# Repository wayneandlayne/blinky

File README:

This is the code for the Blinky POV and Blinky GRID kits from Wayne and Layne.
More information: http://www.wayneandlayne.com/projects/blinky/

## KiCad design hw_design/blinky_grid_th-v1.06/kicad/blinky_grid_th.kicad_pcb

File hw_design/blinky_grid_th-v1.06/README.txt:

Wayne and Layne present:
Blinky Grid TH - Hardware v1.06

These are the design files, for use with Kicad, an open source electronic design suite available for Windows, Linux, and OS X.

More details are available at http://www.wayneandlayne.com/projects/blinky/

Design files: (Located in kicad/ subdirectory)
-------------
blinky_grid_th.brd                  PCB layout
blinky_grid_th.cmp                  Symbol to footprint mapping
blinky_grid_th.net                  Netlist
blinky_grid_th.pro                  Kicad project file
blinky_grid_th.sch                  Schematic
wayne_and_layne_kicad_modules.mod   W&L footprint library
wayne_and_layne_kicad_symbols.lib   W&L symbol library

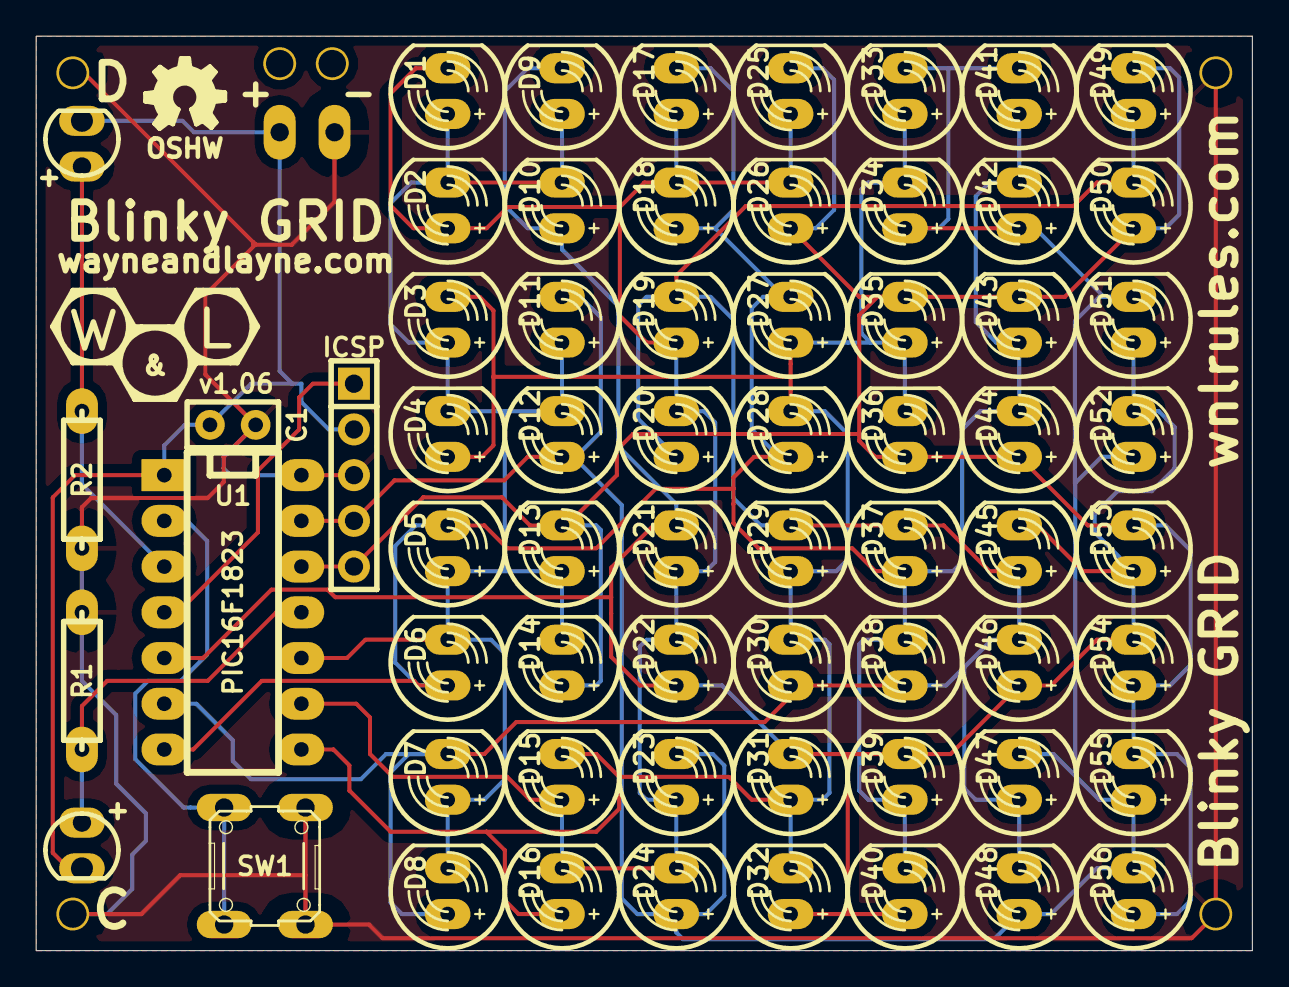
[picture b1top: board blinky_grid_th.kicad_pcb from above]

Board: 2 copper layers, 67.6 x 50.8 mm, 69 parts (0 on the bottom side), 14 nets.

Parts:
BT1: BATTERY; WNL_BATHOLES
C1: C; WNL_C1
D1, D2, D3, D4, D5, D6, D7, D8, D9, D10, D11, D12, D13, D14, D15, D16, D17, D18, D19, D20, D21, D22, D23, D24, D25, D26, D27, D28, D29, D30, D31, D32, D33, D34, D35, D36, D37, D38, D39, D40, D41, D42, D43, D44, D45, D46, D47, D48, D49, D50, D51, D52, D53, D54, D55, D56: LED; LED_5MM_PRETTY_BIGPADS
D57: SCLK; WNL_LIGHTSENSOR_3MM
D58: SDAT; WNL_LIGHTSENSOR_3MM
P1: ICSP; WNL_SIL_5
P2, P3, P4, P5: MOUNT; 1pin60mil
R1, R2: 10K; WNL_R3
SW1: SW_PUSH; WNL_OMRON_6MM_PRETTY
U1: PIC16F1823; WNL_DIP_14_300

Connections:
/BUTTON: SW1.1, U1.2
/LED0: D1.1, D2.2, D3.1, D4.2, D5.1, D6.2, D7.1, D8.2, D9.1, D10.2, D11.1, D12.2, D13.1, D14.2, U1.10
/LED1: D1.2, D2.1, D15.1, D16.2, D17.1, D18.2, D19.1, D20.2, D21.1, D22.2, D23.1, D24.2, D25.1, D26.2, U1.9
/LED2: D3.2, D4.1, D15.2, D16.1, D27.1, D28.2, D29.1, D30.2, D31.1, D32.2, D33.1, D34.2, D35.1, D36.2, U1.8
/LED3: D5.2, D6.1, D17.2, D18.1, D27.2, D28.1, D37.1, D38.2, D39.1, D40.2, D41.1, D42.2, D43.1, D44.2, U1.7
/LED4: D7.2, D8.1, D19.2, D20.1, D29.2, D30.1, D37.2, D38.1, D45.1, D46.2, D47.1, D48.2, D49.1, D50.2, U1.6
/LED5: D9.2, D10.1, D21.2, D22.1, D31.2, D32.1, D39.2, D40.1, D45.2, D46.1, D51.1, D52.2, D53.1, D54.2, U1.5
/LED6: D11.2, D12.1, D23.2, D24.1, D33.2, D34.1, D41.2, D42.1, D47.2, D48.1, D51.2, D52.1, D55.1, D56.2, P1.4, U1.13
/LED7: D13.2, D14.1, D25.2, D26.1, D35.2, D36.1, D43.2, D44.1, D49.2, D50.1, D53.2, D54.1, D55.2, D56.1, P1.5, U1.12
/RESET: P1.1, U1.4
/SCLK: D57.1, R1.2, U1.11
/SDAT: D58.1, R2.2, U1.3
/VDD: BT1.1, C1.1, D57.2, D58.2, P1.2, U1.1
GND: BT1.2, C1.2, P1.3, P2.1, P3.1, P4.1, P5.1, R1.1, R2.1, SW1.2, U1.14

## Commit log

2011-06-06 initial release code for blinky grid, blinky pov, and the bootloader and font table
2012-03-21 updated code to v1.02, only affected the grid and pov userland code, didn't touch the bootloader
2012-04-05 added code for the blinky programming webpage
2012-04-05 added production hex files
2012-04-05 added readme message about the blinkywww code
2012-12-31 fixed silly typo
2012-12-31 added the blinky pov/smt th/smt design files for all releases
2016-01-21 Fixed some confusing comments in the font table.
2016-09-07 Added lots more comments
2016-09-07 Remove tabs and trailing spaces
2016-09-07 Refactor puthex. Add comments. Add all missing if clause curly braces.
2018-03-23 add design files for blinky_grid_smt v1.05
2018-03-23 add design files for blinky_grid_th v1.06
2025-06-25 Move web files into src/
2025-06-25 Remove PHP
2025-06-25 Import blinky programming gif and thumbnail
2025-06-25 Add Playwright tests
2025-06-25 Add additional Playwright tests
2025-06-25 Fix bug with ie message
2025-06-25 Remove add_led_col's unused parameter
2025-06-25 Remove onclick handlers too
    Before removing an LED column, we now
    remove the onclick handlers.
2025-06-25 Remove more onclick handlers
2025-06-25 Use CSS Grid for LED pixels
2025-06-25 Update TODO items
2025-06-25 Adjust styles
2025-06-25 Extract style from HTML
2025-06-25 Update progress bar
2025-06-26 Whitespace
2025-06-26 Extract styles into CSS; inputs to buttons
2025-06-26 Add mobile viewport width to head
2025-06-26 Style images so they can't make the page wider.
2025-06-26 Add lang to html tag
2025-06-26 WIP Adjust layout of data transfer controls
    It's a bit more responsive, and the HTML is definitely more
    modern.
    This also makes real changes that users can see, too.
2025-06-26 Created changelog section
2025-06-26 Increase contrast of link text
